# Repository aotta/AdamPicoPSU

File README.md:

# AdamPicoPSU
Yet another Coleco Adam PicoPSU, cheap and compact

It use a 3 amp 12v regulated PSU for input, and a PICOPSU 20 pin for generate the additional -12v and -5v. A lm7905 converts the -12v to the needed -5v too.
In the BOM also a 1n4148 diode, a 10uf caps, the barrell for input the 12v plug and a 6 pin 7x7 push button for the power on/off, and a db-9 pin for connecting to the ADAM.
Further details in the kicad project and in the "jlcpcb/production_files" subfolder

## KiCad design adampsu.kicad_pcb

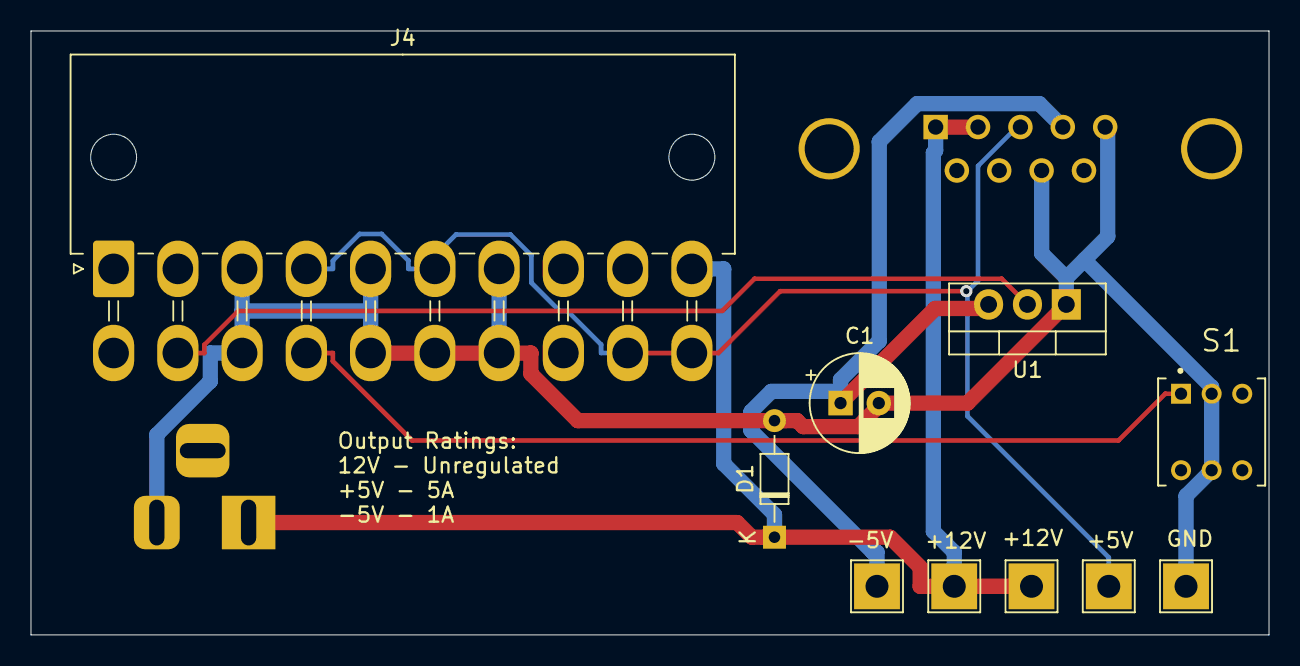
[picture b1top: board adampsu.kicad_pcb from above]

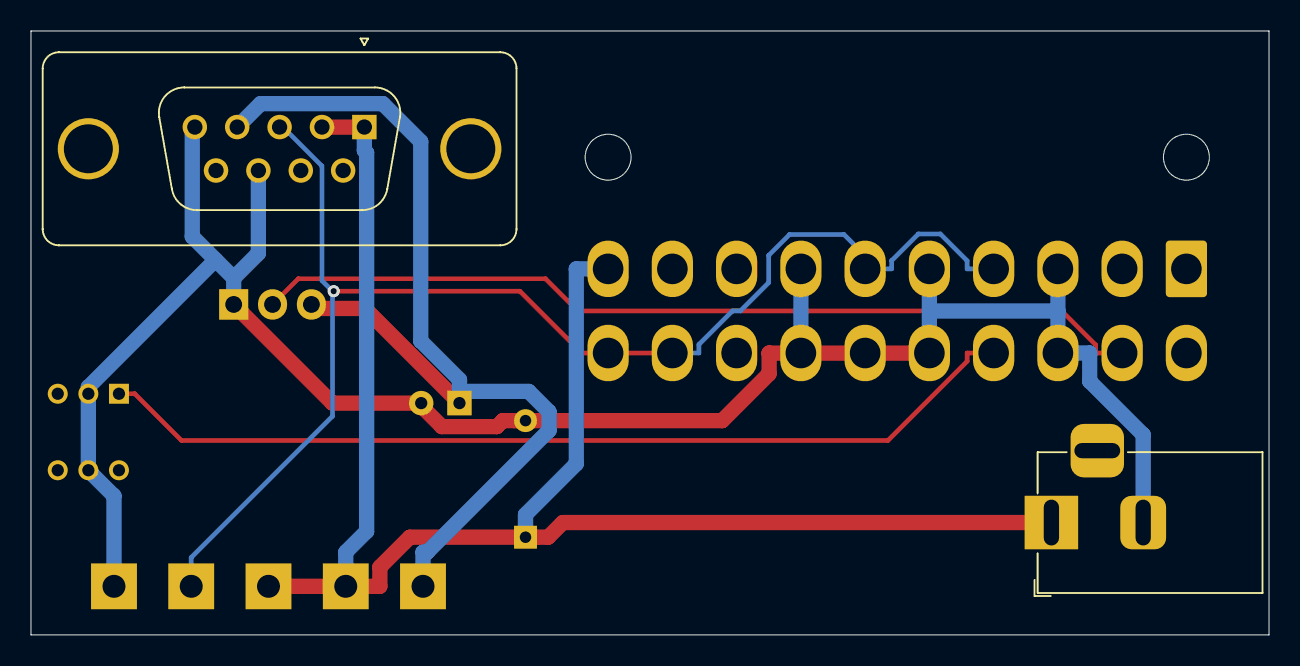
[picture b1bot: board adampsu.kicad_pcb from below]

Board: 2 copper layers, 80.9 x 39.5 mm, 12 parts (2 on the bottom side), 6 nets.

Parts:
C1: 10uf; CP_Radial_D6.3mm_P2.50mm
D1: D_Schottky; D_DO-34_SOD68_P7.62mm_Horizontal
J1: Barrel_Jack_Switch; BarrelJack_Horizontal
J3: DB9_Female; DSUB-9_Female_Vertical_P2.77x2.84mm_MountingHoles
J4: ATX-20; Molex_Mini-Fit_Jr_5569-20A2_2x10_P4.20mm_LargeHoles
S1: TL2230EEF140; SW_TL2230EEF140
TP1: +12VL/Brown; TestPoint_THTPad_3.0x3.0mm_Drill1.5mm
TP2: +12VI/Red; TestPoint_THTPad_3.0x3.0mm_Drill1.5mm
TP3: +5V/Orange; TestPoint_THTPad_3.0x3.0mm_Drill1.5mm
TP4: -5V/Yellow; TestPoint_THTPad_3.0x3.0mm_Drill1.5mm
TP5: GND/Green; TestPoint_THTPad_3.0x3.0mm_Drill1.5mm
U1: L7905; TO-220-3_Vertical

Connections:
+12V: D1.1 (K), J1.1, J3.1, J3.2, J4.10 (+12V), TP1.1, TP2.1
-12V: J4.12 (-12V), U1.2 (VI)
/+5V: J3.3, J4.4 (+5V), J4.6 (+5V), J4.19 (+5V), J4.20 (+5V), TP3.1
/-5V: C1.1, J3.4, TP4.1, U1.3 (VO)
GND: C1.2, D1.2 (A), J1.2, J3.5, J3.8, J4.3 (GND), J4.5 (GND), J4.7 (GND), J4.13 (GND), J4.15 (GND), J4.16 (GND), J4.17 (GND), S1.2, S1.5, TP5.1, U1.1 (GND)
PWON: J4.14 (PS_ON#), S1.1
